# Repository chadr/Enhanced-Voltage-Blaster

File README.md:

# Enhanced Voltage Blaster
 A (slightly) enhanced version of the original Voltage Blaster by PhilsComputerLab and Necroware [here](https://youtu.be/y1-0giyLQIY).

**Enhancements:**
* Diodes protect regulator from reverse polarity and reverse bias. Prevents soundcard-frying over voltage.
* Four LEDs show presence of the four main power rails on the ISA bus.
* Dual copper heatsink pads embedded into PCB design to keep regulator cool.
* Jumper to disable Voltage Blaster without removal. Can be used to verify lack of (-)5V on ISA bus.

The datasheet for the 79xx series negative regulators strongly recommend two protection diodes. PCs get shutdown suddenly and sound cards have lots of capacitance. The exact two situations described here.

**Bill of Materials**
**Item**|**Qty**|**MFG Part Num**|**Mouser Part Num**
:-----:|:-----:|:-----:|:-----:
Neg 5V Linear Regulator|1|MC79M05CDT|863-MC79M05CDT
22uF 35V Electrolytic Capacitor|2|860010572003|710-860010572003
5mm Red LED Diffused|4|WP7113ID|604-WP7113ID
330R Metal Film Resistor 1%|2|MFR-25FRF52-330R|603-MFR-25FRF52-330R
1K Metal Film Resistor 1%|2|MFR-25FRF52-1K|603-MFR-25FRF52-1K
Schottky Diode 40 Volt 1.0 Amp|2|SB140-E3/73|625-SB140-E3/73

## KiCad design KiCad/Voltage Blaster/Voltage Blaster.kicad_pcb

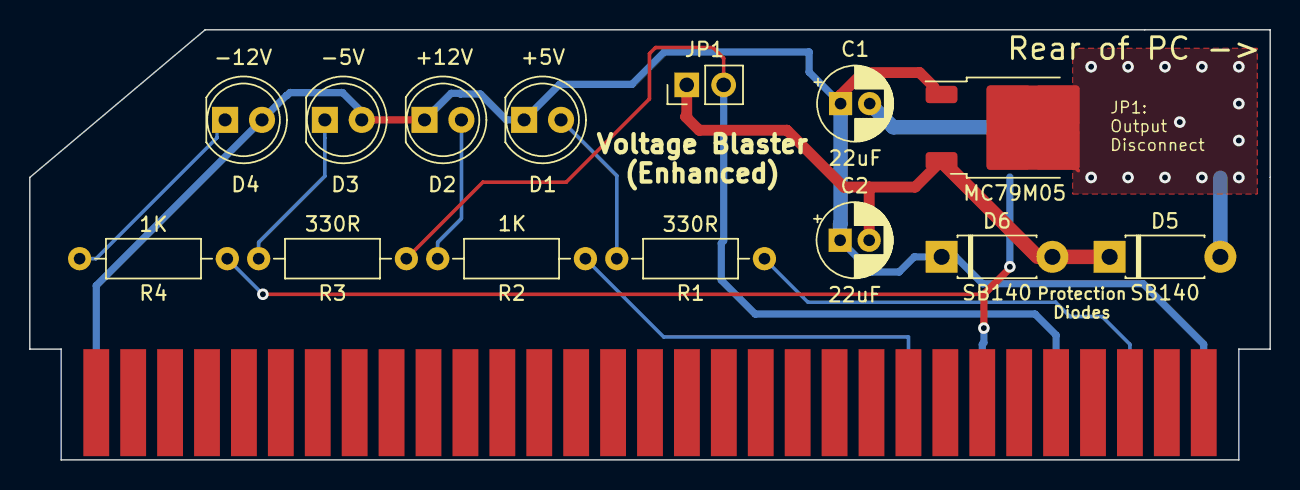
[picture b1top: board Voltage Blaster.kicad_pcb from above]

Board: 2 copper layers, 85.3 x 29.6 mm, 16 parts (1 on the bottom side), 10 nets.

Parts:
C1, C2: 22uF; CP_Radial_D5.0mm_P2.00mm
D1: +5V; LED_D5.0mm
D2: +12V; LED_D5.0mm
D3: -5V; LED_D5.0mm
D4: -12V; LED_D5.0mm
D5, D6: SB140; D_DO-41_SOD81_P7.62mm_Horizontal
J1: Bus_ISA_8bit_AB_Rev0; ISA_CARD_EDGE_CONNECTOR_8BIT_Rev1
JP1: Output Disconnect; PinHeader_1x02_P2.54mm_Vertical
Open Hardware Logo: OSHW-Logo2_7.3x6mm_SilkScreen
R1, R3: 330R; R_Axial_DIN0207_L6.3mm_D2.5mm_P10.16mm_Horizontal
R2, R4: 1K; R_Axial_DIN0207_L6.3mm_D2.5mm_P10.16mm_Horizontal
U1: MC79M05; TO-252-2

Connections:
+5V: J1.B03 (VCC), R1.1
+12V: J1.B09 (+12V), R2.1
-5V: J1.B05 (-5V), JP1.2 (B), R3.1
-12V: C1.2, D5.2 (A), J1.B07 (-12V), R4.1, U1.2 (VI)
/VO: C2.2, D5.1 (K), D6.2 (A), JP1.1 (A), U1.3 (VO)
GND: C1.1, C2.1, D1.1 (K), D2.1 (K), D3.2 (A), D4.2 (A), D6.1 (K), J1.B01 (GND), J1.B31 (GND), U1.1 (GND)
unnamed: D1.2 (A), R1.2
unnamed: D2.2 (A), R2.2
unnamed: D3.1 (K), R3.2
unnamed: D4.1 (K), R4.2

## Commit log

2023-11-03 update silkscreen
2024-01-31 add image
2024-02-16 update image
2024-02-17 add to docs
2024-03-02 add img
2024-04-22 add instructions
